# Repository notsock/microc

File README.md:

# microc
Sparkfun Pro Micro compatible board with USB-C support

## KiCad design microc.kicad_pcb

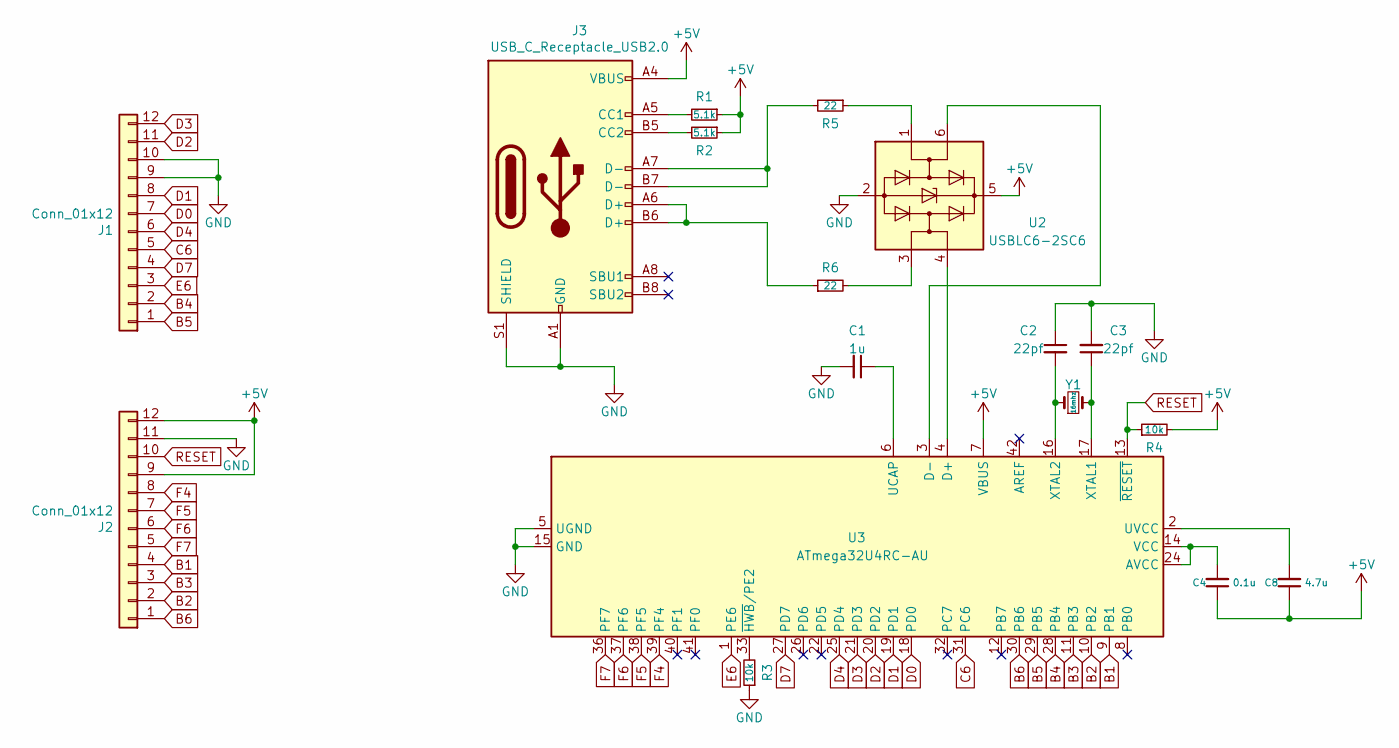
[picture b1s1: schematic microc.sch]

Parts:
C1: 1u; C_0603_1608Metric
C2, C3: 22pf; C_0603_1608Metric
C4: 0.1u; C_0603_1608Metric
C8: 4.7u; C_0603_1608Metric
J1, J2: Conn_01x12; PinSocket_1x12_P2.54mm_Vertical
J3: USB_C_Receptacle_USB2.0; USB-C_16P_Midmount
R1, R2: 5.1k; R_0603_1608Metric
R3, R4: 10k; R_0603_1608Metric
R5, R6: 22; R_0603_1608Metric
U2: USBLC6-2SC6; SOT-23-6
U3: ATmega32U4RC-AU; TQFP-44_10x10mm_P0.8mm
Y1: 16mhz; Crystal_SMD_5032-2Pin_5.0x3.2mm_HandSoldering

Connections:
+5V: C4.1, C8.1, J2.9, J2.12, J3.A4 (VBUS), J3.A9 (VBUS), J3.B4 (VBUS), J3.B9 (VBUS), R1.1, R2.1, R4.2, U2.5 (VBUS), U3.7 (VBUS)
B1: J2.4, U3.9 (PB1)
B2: J2.2, U3.10 (PB2)
B3: J2.3, U3.11 (PB3)
B4: J1.2, U3.28 (PB4)
B5: J1.1, U3.29 (PB5)
B6: J2.1, U3.30 (PB6)
C6: J1.5, U3.31 (PC6)
D0: J1.7, U3.18 (PD0)
D1: J1.8, U3.19 (PD1)
D2: J1.11, U3.20 (PD2)
D3: J1.12, U3.21 (PD3)
D4: J1.6, U3.25 (PD4)
D7: J1.4, U3.27 (PD7)
E6: J1.3, U3.1 (PE6)
F4: J2.8, U3.39 (PF4)
F5: J2.7, U3.38 (PF5)
F6: J2.6, U3.37 (PF6)
F7: J2.5, U3.36 (PF7)
GND: C1.2, C2.1, C3.2, J1.9, J1.10, J2.11, J3.A1 (GND), J3.A12 (GND), J3.B1 (GND), J3.B12 (GND), J3.S1 (SHIELD), R3.1, U2.2 (GND), U3.5 (UGND), U3.15 (GND), U3.23 (GND), U3.35 (GND), U3.43 (GND)
unnamed: C1.1, U3.6 (UCAP)
unnamed: C2.2, U3.16 (XTAL2), Y1.1
unnamed: C3.1, U3.17 (XTAL1), Y1.2
unnamed: C4.2, U3.14 (VCC), U3.24 (AVCC), U3.34 (VCC), U3.44 (AVCC)
unnamed: C8.2, U3.2 (UVCC)
unnamed: J3.A5 (CC1), R1.2
unnamed: J3.A6 (D+), J3.B6 (D+), R6.1
unnamed: J3.A7 (D-), J3.B7 (D-), R5.2
unnamed: J3.B5 (CC2), R2.2
unnamed: R3.2, U3.33 (~HWB~/PE2)
unnamed: R5.1, U2.1 (I/O1)
unnamed: R6.2, U2.3 (I/O2)
unnamed: U2.4 (I/O2), U3.4 (D+)
unnamed: U2.6 (I/O1), U3.3 (D-)
RESET: J2.10, R4.1, U3.13 (~RESET)

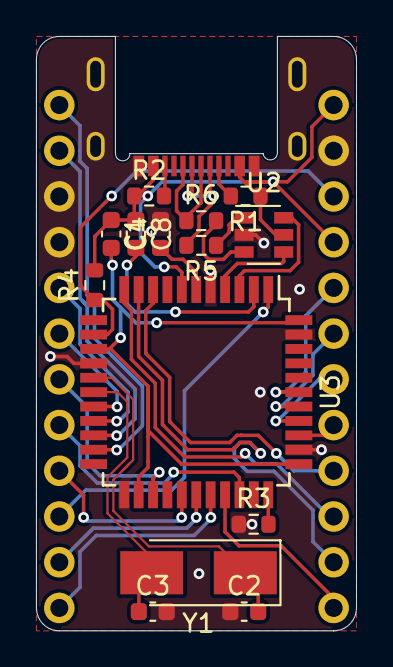
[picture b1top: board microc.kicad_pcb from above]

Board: 2 copper layers, 17.8 x 33.0 mm, 17 parts (0 on the bottom side), 35 nets.

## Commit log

2021-07-26 i give up
2021-07-27 rev 1 - Completed PCB - Completed schematic
    Notes:
    - Added 0 ohm resistor to schematic in order to help with routing
2021-07-27 rev1.1 - Added crystal to PCB
2021-07-27 rev1.2 - Removed 0 ohm resistor and replaced with via
2021-07-27 rev1.2 - Aesthetic updates to PCB
2021-07-29 rev 1.3 - Improved ground plane - Updated routing - Fixed error with power in schematic
